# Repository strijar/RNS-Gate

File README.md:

# RNS-Gate

## Objective

Create a standalone device for access and routing within the Reticulum Network Stack 

## Interfaces for accessing other network nodes

* Integrated:
  - LoRa module (E22/E32 via SPI)
  - WiFi
  - Bluetooth
  - 10/100 Ethernet
* External:
  - RNode (via USB or Bluetooth)
  - WiFi in monitor mode (via USB)
* Audio access and PTT control for connecting analog VHF and HF radios with soft modem implementation 
* Connection of DMR stations via USB (OpenGD77 firmware) 

## Access to user devices

* BlueTooth 
* IP via WiFi and Ethernet

## Implementation

A 3-component "tower":

* Single-board computer based on Orange Pi Zero 
* Add-on board with an E22/E32 LoRa module 
* Add-on board with an HF/VHF audio interface

## Device configuration

Web interface over IP

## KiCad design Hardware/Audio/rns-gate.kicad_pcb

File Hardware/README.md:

# RNS-Gate Hardware

## Audio cable pinout

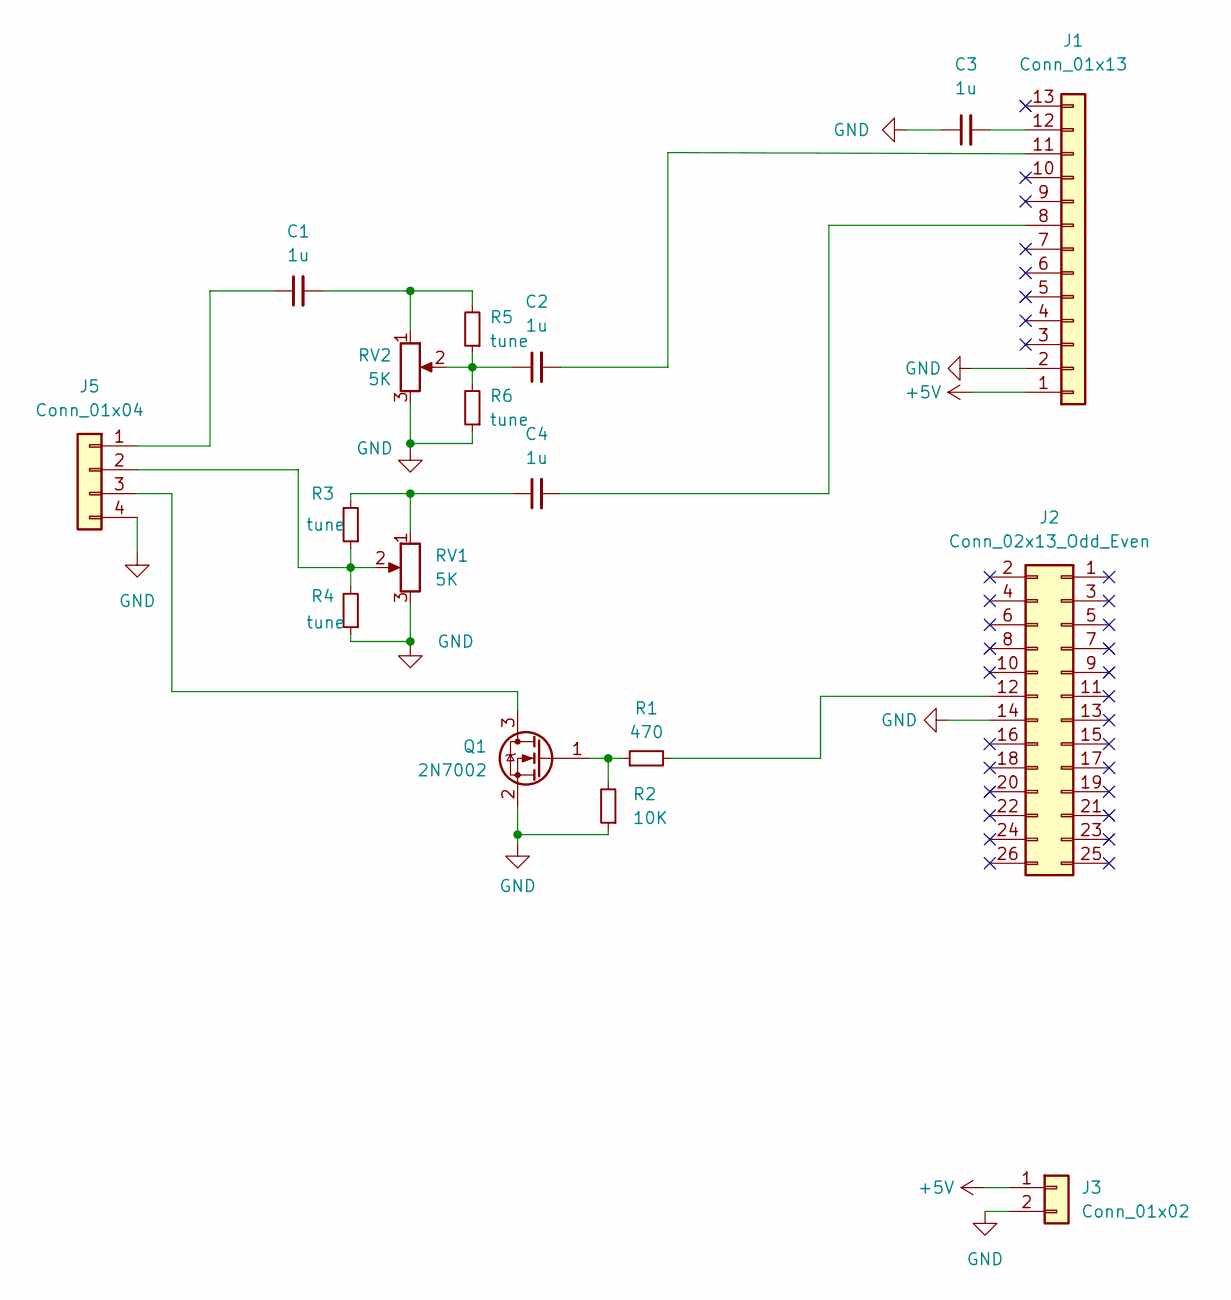
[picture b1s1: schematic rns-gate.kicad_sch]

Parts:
C1, C2, C3, C4: 1u; C_0805_2012Metric
J1: Conn_01x13; PinHeader_1x13_P2.54mm_Vertical
J2: Conn_02x13_Odd_Even; PinHeader_2x13_P2.54mm_Vertical
J3: Conn_01x02; PinHeader_1x02_P2.54mm_Vertical
J5: Conn_01x04; PinHeader_1x04_P2.54mm_Vertical
Q1: 2N7002; SOT-23
R1: 470; R_0805_2012Metric
R2: 10K; R_0805_2012Metric
R3, R4, R5, R6: tune; R_0805_2012Metric
RV1, RV2: 5K; Potentiometer_Bourns_3296W_Vertical

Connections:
+5V: J1.1, J3.1
GND: C3.1, J1.2, J2.14, J3.2, J5.4, Q1.2 (S), R2.1, R4.1, R6.1, RV1.3, RV2.3
unnamed: C2.1, R5.1, R6.2, RV2.2
unnamed: C2.2, J1.11
unnamed: C3.2, J1.12
unnamed: C4.1, R3.2, RV1.1
unnamed: C4.2, J1.8
unnamed: J2.12, R1.2
unnamed: C1.1, J5.1
unnamed: J5.3, Q1.3 (D)
unnamed: Q1.1 (G), R1.1, R2.2
unnamed: J5.2, R3.1, R4.2, RV1.2
unnamed: C1.2, R5.2, RV2.1

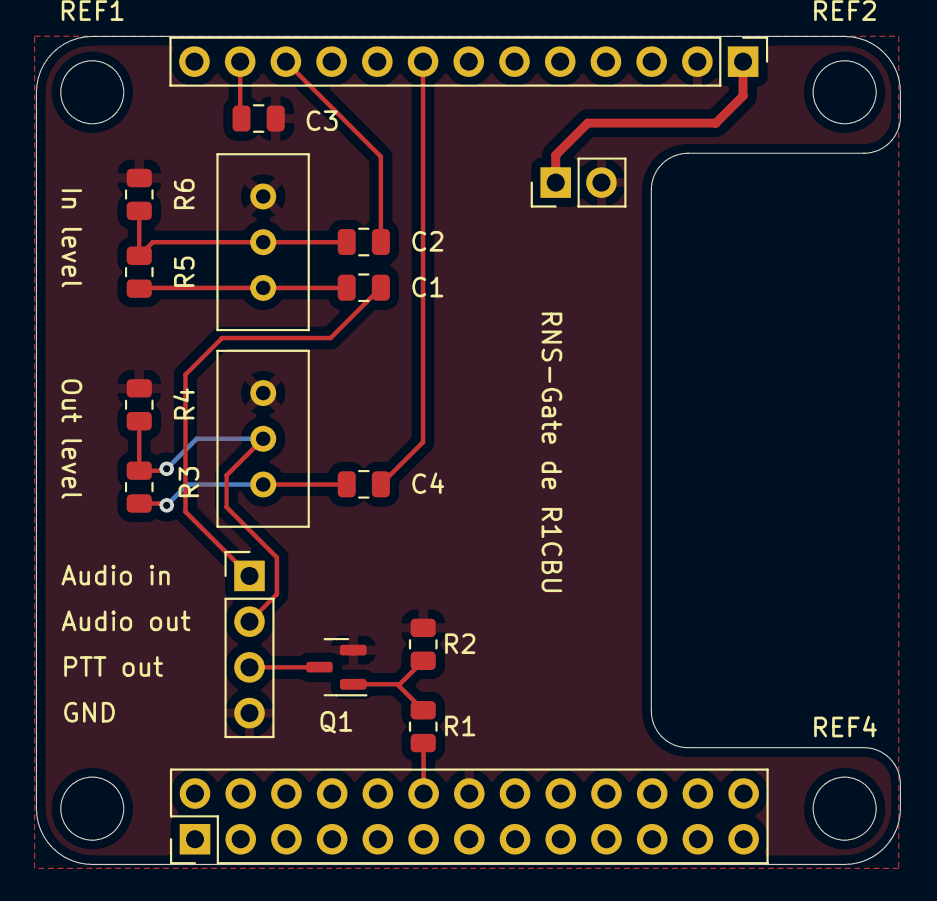
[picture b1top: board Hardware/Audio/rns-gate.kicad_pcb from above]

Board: 2 copper layers, 48.0 x 46.0 mm, 21 parts (0 on the bottom side), 13 nets.

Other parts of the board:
REF1, REF2, REF3, REF4: MountingHole_3.5mm

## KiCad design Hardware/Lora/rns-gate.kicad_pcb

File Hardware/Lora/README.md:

# RNS-Gate Hardware

## Lora module

### Pinout

| E22  | Orange Pi Zero                |
|------|-------------------------------|
| SPI  | SPI1 (PA13, PA14, PA15, PA16) |
| Busy | PA11                          |
| NRST | PA06                          |
| DIO1 | PA12                          |
| DIO2 | PA19                          |
| RXEN | PA02                          |
| TXEN | PA18                          |

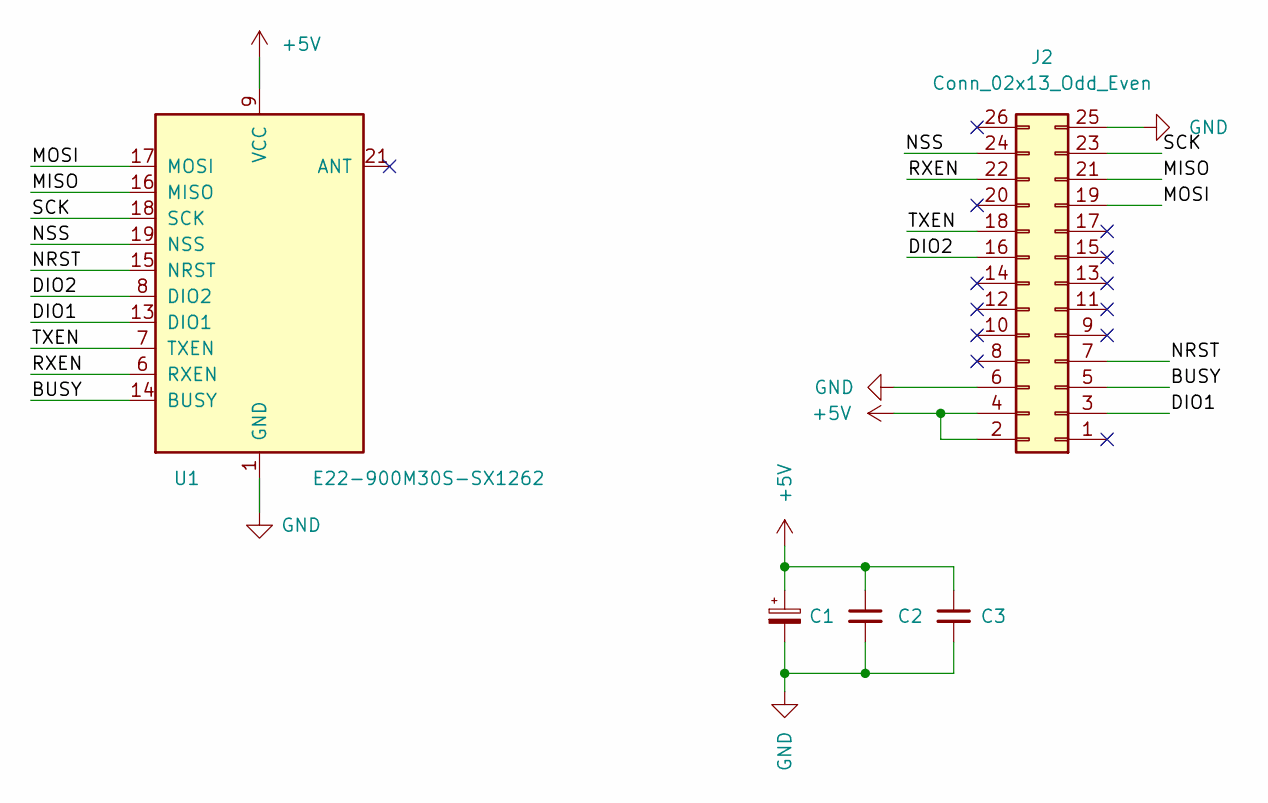
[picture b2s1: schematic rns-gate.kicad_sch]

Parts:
C1: C_Polarized_Small; CP_EIA-7343-43_Kemet-X_Pad2.25x2.55mm_HandSolder
C2, C3: C_Small; C_0805_2012Metric_Pad1.18x1.45mm_HandSolder
J2: Conn_02x13_Odd_Even; PinHeader_2x13_P2.54mm_Vertical
U1: E22-900M30S-SX1262

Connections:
+5V: C1.1, C2.1, C3.1, J2.2, J2.4, U1.9 (VCC), U1.10 (VCC)
/BUSY: J2.5, U1.14 (BUSY)
/DIO1: J2.3, U1.13 (DIO1)
/DIO2: J2.16, U1.8 (DIO2)
/MISO: J2.21, U1.16 (MISO)
/MOSI: J2.19, U1.17 (MOSI)
/NRST: J2.7, U1.15 (NRST)
/NSS: J2.24, U1.19 (NSS)
/RXEN: J2.22, U1.6 (RXEN)
/SCK: J2.23, U1.18 (SCK)
/TXEN: J2.18, U1.7 (TXEN)
GND: C1.2, C2.2, C3.2, J2.6, J2.25, U1.1 (GND), U1.2 (GND), U1.3 (GND), U1.4 (GND), U1.5 (GND), U1.11 (GND), U1.12 (GND), U1.20 (GND), U1.22 (GND)

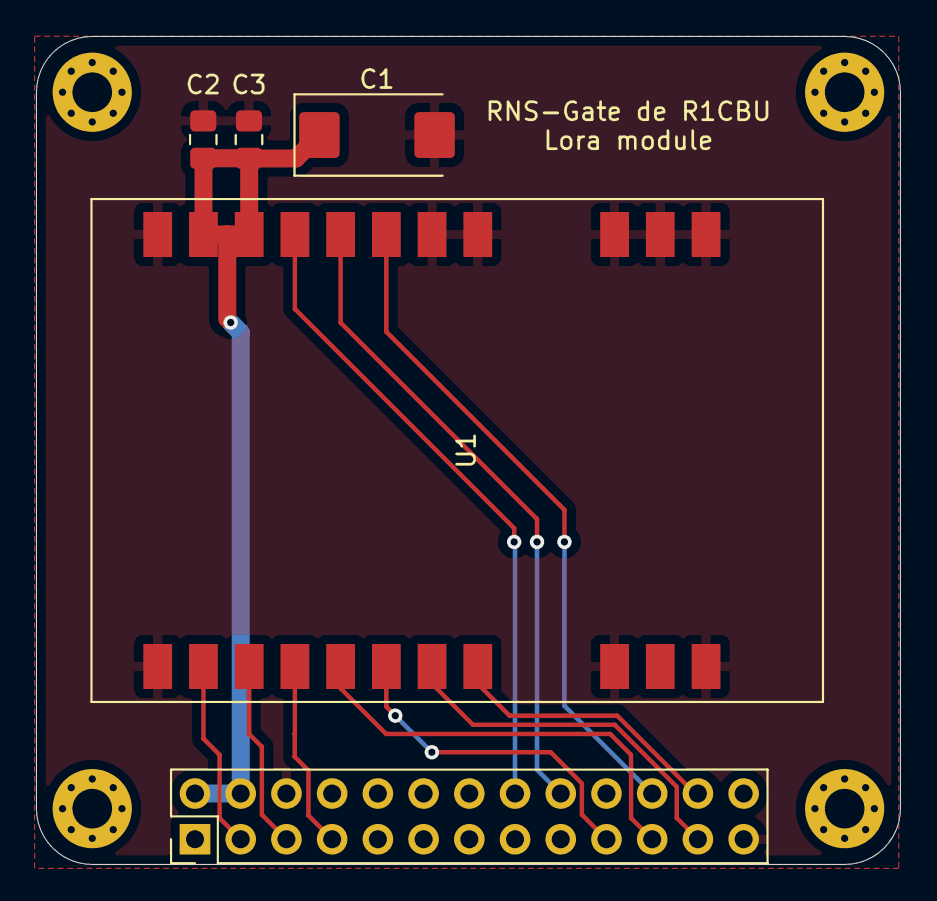
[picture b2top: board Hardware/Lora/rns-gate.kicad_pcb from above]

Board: 2 copper layers, 48.0 x 46.0 mm, 9 parts (0 on the bottom side), 12 nets.

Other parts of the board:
REF1, REF2, REF3, REF4: MountingHole_2.2mm_M2_Pad_Via

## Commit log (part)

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2025-09-29 Initial sources
2025-09-29 Kernel dts and config
2025-09-29 RAEDME
2025-09-29 Fixes. Add rns package. Update config
2025-09-30 Update config (NetworkManager, DBus, lighttpd)
2025-09-30 Add lxmf package. Update config
2025-10-13 Alsa config
2025-10-26 Update configs
2025-10-31 Switch to Buildroot 2024.02
2025-11-01 Update BR and added pulseaudio configs
2025-11-01 Added hardware - Lora module
2025-11-01 Added hardware - Audio module
2025-11-01 Added hardware modules pictures
2025-11-13 Added PDF schematics
2025-11-17 Added some pictures of hardware
2025-11-17 Added Lora module pinout
2025-12-02 Update rns and lxmf package
2025-12-07 Added packages, FAT part in image
2025-12-16 Update start scripts
2025-12-17 Added RNode package and config
2025-12-19 Added nomadnet package
2025-12-24 Update nomadnet package
2026-01-02 Added led control
2026-01-02 Add audio pinout
2026-01-02 File name fix
2026-01-02 Edit readme
2026-01-04 Nomadnet config
2026-01-22 Added pos files for PCB
2026-01-23 WiFi fix
2026-01-23 More correct access rights on the FAT partition
2026-01-23 Update rns and nomadnet packages
2026-01-28 Update Lora module
2026-01-28 Update Lora schematic
2026-02-03 Remove NetworkManager and DBus. Add fsck for mnt
2026-02-03 Set CPU Freq (fixing freezes)
2026-02-03 Added USB RNode to rns config
2026-02-03 Fixed group for rns user (for USB RNode)
2026-02-04 WiFi support (via wpa_cli)
2026-02-07 Update RNode
2026-02-08 Change nomadnet to lxmd + rns-page-node
2026-03-07 Remove CPU Freq (but fixed freezes)
2026-03-14 Update RNode, revert cpu freq, turn off start lxmfd
2026-04-18 Update rns
2026-04-18 Improvements for better reliability (freezes)
2026-04-21 Update rns config
2026-04-27 Added rns-rs package
2026-04-30 Update rns-rs package
2026-05-21 Migrate to 2026.02 and Rust Reticulum/LXMF
2026-05-25 Update rs-reticulum
2026-05-25 Update rs-lxmf
2026-06-12 Update rns-rs, lxmf-rs, config. Cleanup
2026-06-12 Update rns-rs
2026-06-19 Update rs-lxmf, rs-reticulum
2026-06-27 Added freedv-tnc package
